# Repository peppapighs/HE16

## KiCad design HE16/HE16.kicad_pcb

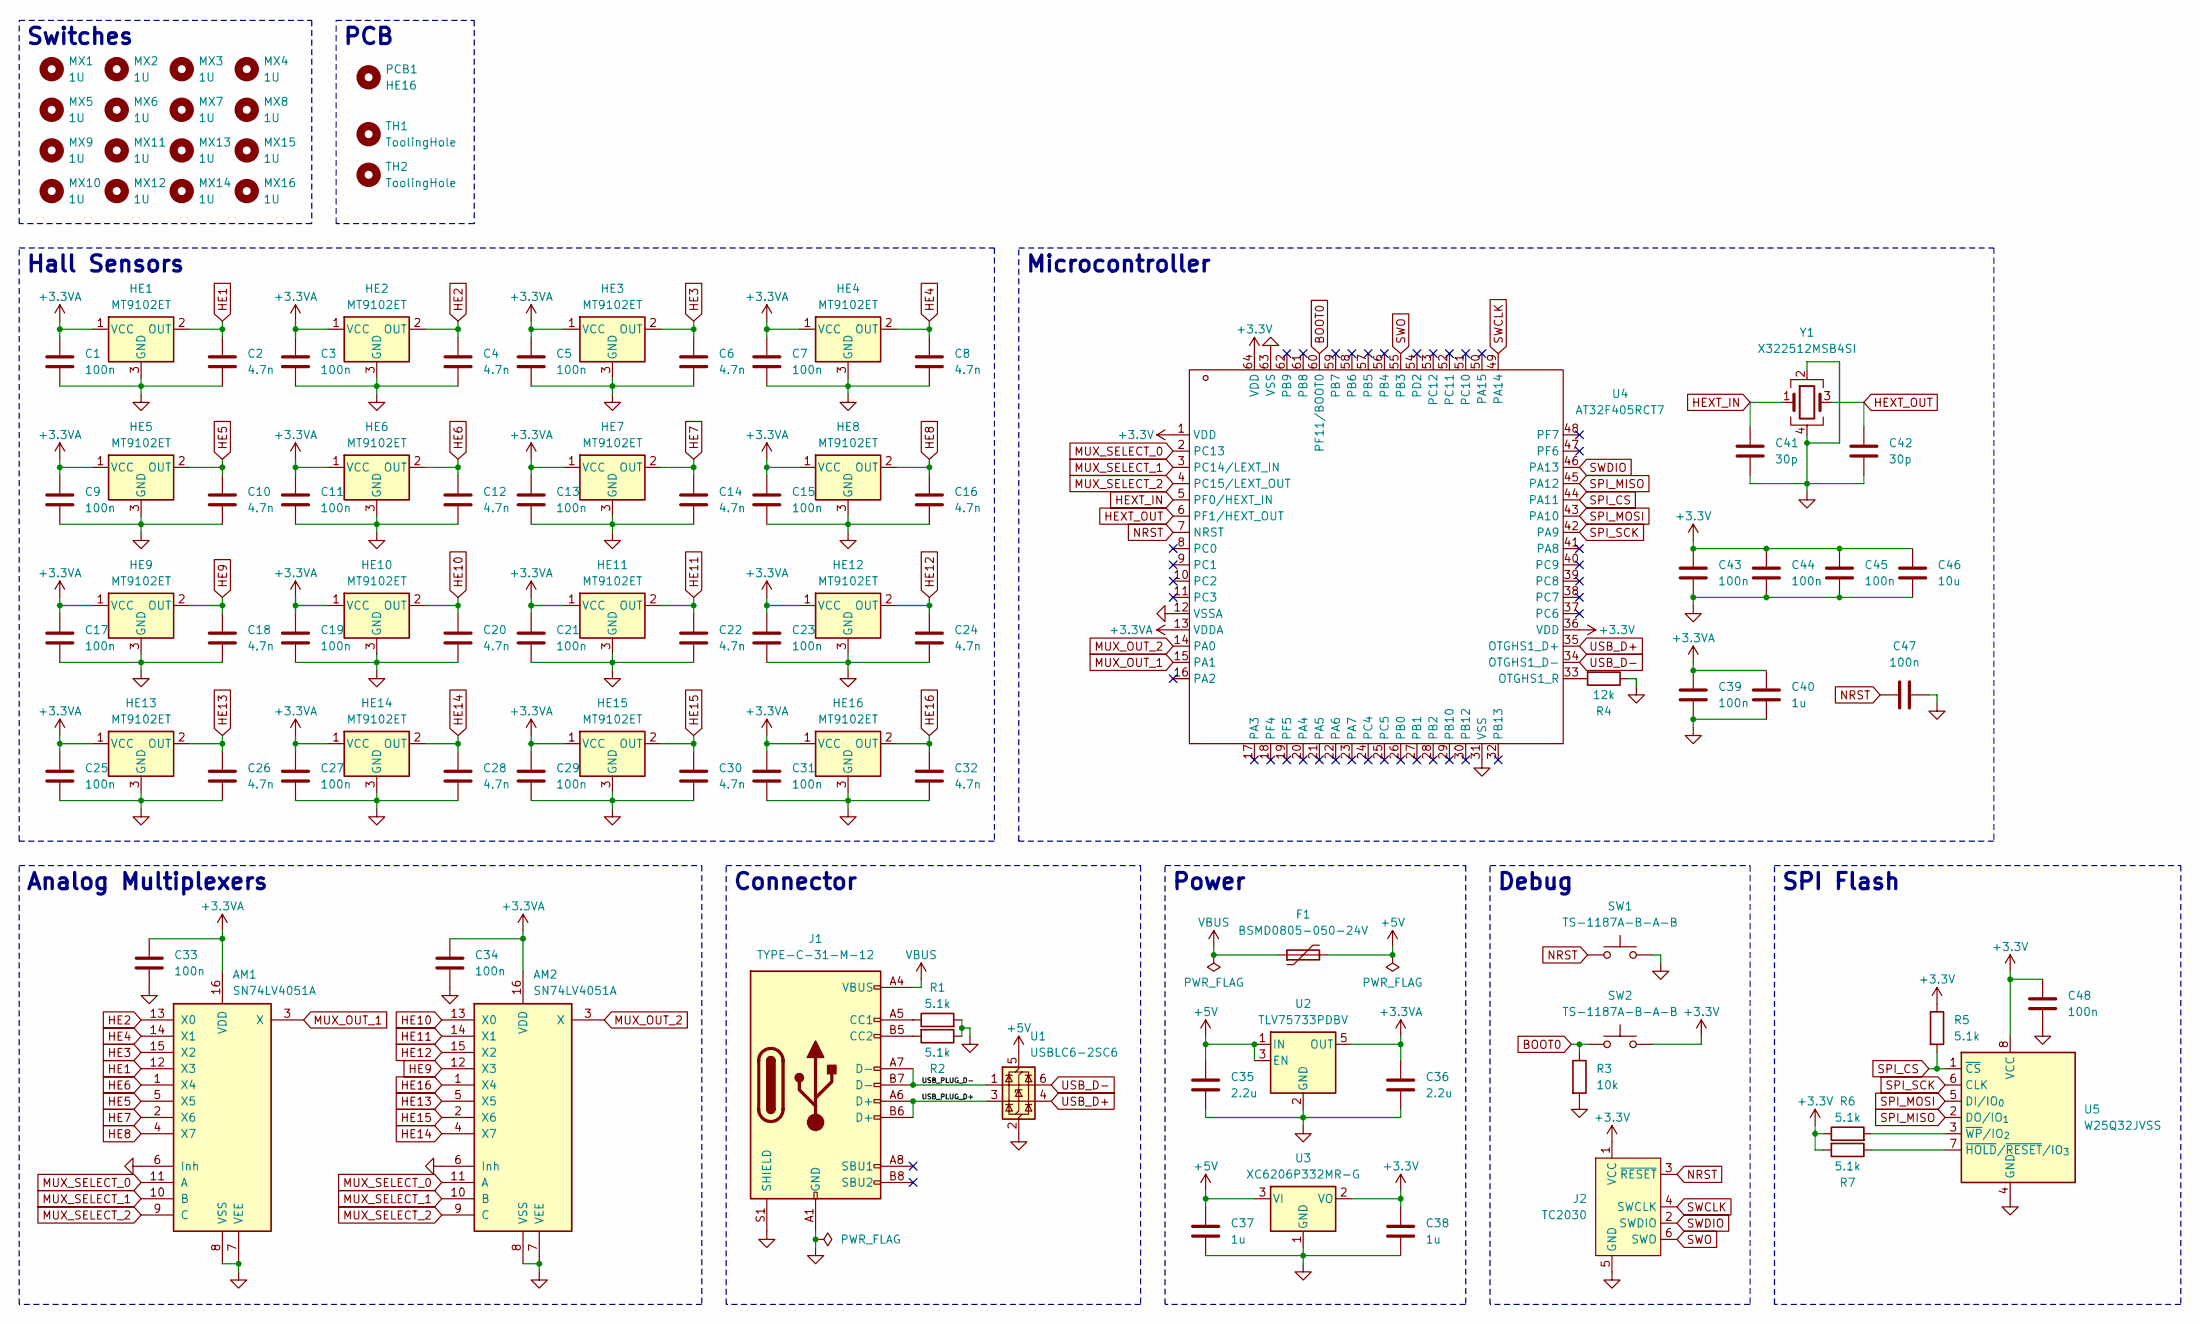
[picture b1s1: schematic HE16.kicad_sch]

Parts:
AM1, AM2: SN74LV4051A; TSSOP-16_4.4x5mm_P0.65mm
C1, C3, C5, C7, C9, C11, C13, C15, C17, C19, C21, C23, C25, C27, C29, C31, C33, C34, C39, C43, C44, C45, C47, C48: 100n; C_0402_1005Metric
C2, C4, C6, C8, C10, C12, C14, C16, C18, C20, C22, C24, C26, C28, C30, C32: 4.7n; C_0402_1005Metric
C35, C36: 2.2u; C_0603_1608Metric
C37, C38, C40: 1u; C_0603_1608Metric
C41, C42: 30p; C_0603_1608Metric
C46: 10u; C_0603_1608Metric
F1: BSMD0805-050-24V; Fuse_0805_2012Metric
HE1, HE2, HE3, HE4, HE5, HE6, HE7, HE8, HE9, HE10, HE11, HE12, HE13, HE14, HE15, HE16: MT9102ET; SOT-23-3
J1: TYPE-C-31-M-12; USB_C_Receptacle_HRO_TYPE-C-31-M-12
J2: TC2030; Tag-Connect_TC2030-IDC-FP_2x03_P1.27mm_Vertical
MX1, MX2, MX3, MX4, MX5, MX6, MX7, MX8, MX9, MX10, MX11, MX12, MX13, MX14, MX15, MX16: 1U; MX-1U
PCB1: HE16
R1, R2, R5, R6, R7: 5.1k; R_0402_1005Metric
R3: 10k; R_0402_1005Metric
R4: 12k; R_0402_1005Metric
SW1, SW2: TS-1187A-B-A-B; SW_Push_1P1T_XKB_TS-1187A
TH1, TH2: ToolingHole
U1: USBLC6-2SC6; SOT-23-6
U2: TLV75733PDBV; SOT-23-5
U3: XC6206P332MR-G; SOT-23-3
U4: AT32F405RCT7; LQFP-64_10x10mm_P0.5mm
U5: W25Q32JVSS; SOIC-8_5.3x5.3mm_P1.27mm
Y1: X322512MSB4SI; Crystal_SMD_3225-4Pin_3.2x2.5mm

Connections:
+3.3V: C38.1, C43.1, C44.1, C45.1, C46.1, C48.1, J2.1 (VCC), R5.1, R6.1, R7.2, SW2.2, U3.2 (VO), U4.1 (VDD), U4.36 (VDD), U4.64 (VDD), U5.8 (VCC)
+3.3VA: AM1.16 (VDD), AM2.16 (VDD), C1.1, C3.1, C5.1, C7.1, C9.1, C11.1, C13.1, C15.1, C17.1, C19.1, C21.1, C23.1, C25.1, C27.1, C29.1, C31.1, C33.1, C34.1, C36.1, C39.1, C40.1, HE1.1 (VCC), HE2.1 (VCC), HE3.1 (VCC), HE4.1 (VCC), HE5.1 (VCC), HE6.1 (VCC), HE7.1 (VCC), HE8.1 (VCC), HE9.1 (VCC), HE10.1 (VCC), HE11.1 (VCC), HE12.1 (VCC), HE13.1 (VCC), HE14.1 (VCC), HE15.1 (VCC), HE16.1 (VCC), U2.5 (OUT), U4.13 (VDDA)
+5V: C35.1, C37.1, F1.2, U1.5 (VBUS), U2.1 (IN), U2.3 (EN), U3.3 (VI)
/USB_PLUG_D+: J1.A6 (D+), J1.B6 (D+), U1.3 (I/O2)
/USB_PLUG_D-: J1.A7 (D-), J1.B7 (D-), U1.1 (I/O1)
BOOT0: R3.1, SW2.1, U4.60 (PF11/BOOT0)
GND: AM1.6 (Inh), AM1.7 (VEE), AM1.8 (VSS), AM2.6 (Inh), AM2.7 (VEE), AM2.8 (VSS), C1.2, C2.2, C3.2, C4.2, C5.2, C6.2, C7.2, C8.2, C9.2, C10.2, C11.2, C12.2, C13.2, C14.2, C15.2, C16.2, C17.2, C18.2, C19.2, C20.2, C21.2, C22.2, C23.2, C24.2, C25.2, C26.2, C27.2, C28.2, C29.2, C30.2, C31.2, C32.2, C33.2, C34.2, C35.2, C36.2, C37.2, C38.2, C39.2, C40.2, C41.2, C42.2, C43.2, C44.2, C45.2, C46.2, C47.2, C48.2, HE1.3 (GND), HE2.3 (GND), HE3.3 (GND), HE4.3 (GND), HE5.3 (GND), HE6.3 (GND), HE7.3 (GND), HE8.3 (GND), HE9.3 (GND), HE10.3 (GND), HE11.3 (GND), HE12.3 (GND), HE13.3 (GND), HE14.3 (GND), HE15.3 (GND), HE16.3 (GND), J1.A1 (GND), J1.A12 (GND), J1.B1 (GND), J1.B12 (GND), J1.S1 (SHIELD), J2.5 (GND), R1.2, R2.1, R3.2, R4.1, SW1.2, U1.2 (GND), U2.2 (GND), U3.1 (GND), U4.12 (VSSA), U4.31 (VSS), U4.63 (VSS), U5.4 (GND), Y1.2, Y1.4
HE1: AM1.12 (X3), C2.1, HE1.2 (OUT)
HE2: AM1.13 (X0), C4.1, HE2.2 (OUT)
HE3: AM1.15 (X2), C6.1, HE3.2 (OUT)
HE4: AM1.14 (X1), C8.1, HE4.2 (OUT)
HE5: AM1.5 (X5), C10.1, HE5.2 (OUT)
HE6: AM1.1 (X4), C12.1, HE6.2 (OUT)
HE7: AM1.2 (X6), C14.1, HE7.2 (OUT)
HE8: AM1.4 (X7), C16.1, HE8.2 (OUT)
HE9: AM2.12 (X3), C18.1, HE9.2 (OUT)
HE10: AM2.13 (X0), C20.1, HE10.2 (OUT)
HE11: AM2.14 (X1), C22.1, HE11.2 (OUT)
HE12: AM2.15 (X2), C24.1, HE12.2 (OUT)
HE13: AM2.5 (X5), C26.1, HE13.2 (OUT)
HE14: AM2.4 (X7), C28.1, HE14.2 (OUT)
HE15: AM2.2 (X6), C30.1, HE15.2 (OUT)
HE16: AM2.1 (X4), C32.1, HE16.2 (OUT)
HEXT_IN: C41.1, U4.5 (PF0/HEXT_IN), Y1.1
HEXT_OUT: C42.1, U4.6 (PF1/HEXT_OUT), Y1.3
MUX_OUT_1: AM1.3 (X), U4.15 (PA1)
MUX_OUT_2: AM2.3 (X), U4.14 (PA0)
MUX_SELECT_0: AM1.11 (A), AM2.11 (A), U4.2 (PC13)
MUX_SELECT_1: AM1.10 (B), AM2.10 (B), U4.3 (PC14/LEXT_IN)
MUX_SELECT_2: AM1.9 (C), AM2.9 (C), U4.4 (PC15/LEXT_OUT)
NRST: C47.1, J2.3 (~RESET), SW1.1, U4.7 (NRST)
unnamed: J1.A5 (CC1), R1.1
unnamed: J1.B5 (CC2), R2.2
unnamed: R4.2, U4.33 (OTGHS1_R)
unnamed: R7.1, U5.7 (~HOLD/~RESET/IO_{3})
unnamed: R6.2, U5.3 (~WP/IO_{2})
SPI_CS: R5.2, U4.44 (PA11), U5.1 (~CS)
SPI_MISO: U4.45 (PA12), U5.2 (DO/IO_{1})
SPI_MOSI: U4.43 (PA10), U5.5 (DI/IO_{0})
SPI_SCK: U4.42 (PA9), U5.6 (CLK)
SWCLK: J2.4 (SWCLK), U4.49 (PA14)
SWDIO: J2.2 (SWDIO), U4.46 (PA13)
SWO: J2.6 (SWO), U4.55 (PB3)
USB_D+: U1.4 (I/O2), U4.35 (OTGHS1_D+)
USB_D-: U1.6 (I/O1), U4.34 (OTGHS1_D-)
VBUS: F1.1, J1.A4 (VBUS), J1.A9 (VBUS), J1.B4 (VBUS), J1.B9 (VBUS)

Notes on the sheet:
Switches
Connector
Debug
Microcontroller
Analog Multiplexers
Hall Sensors
PCB
SPI Flash
Power

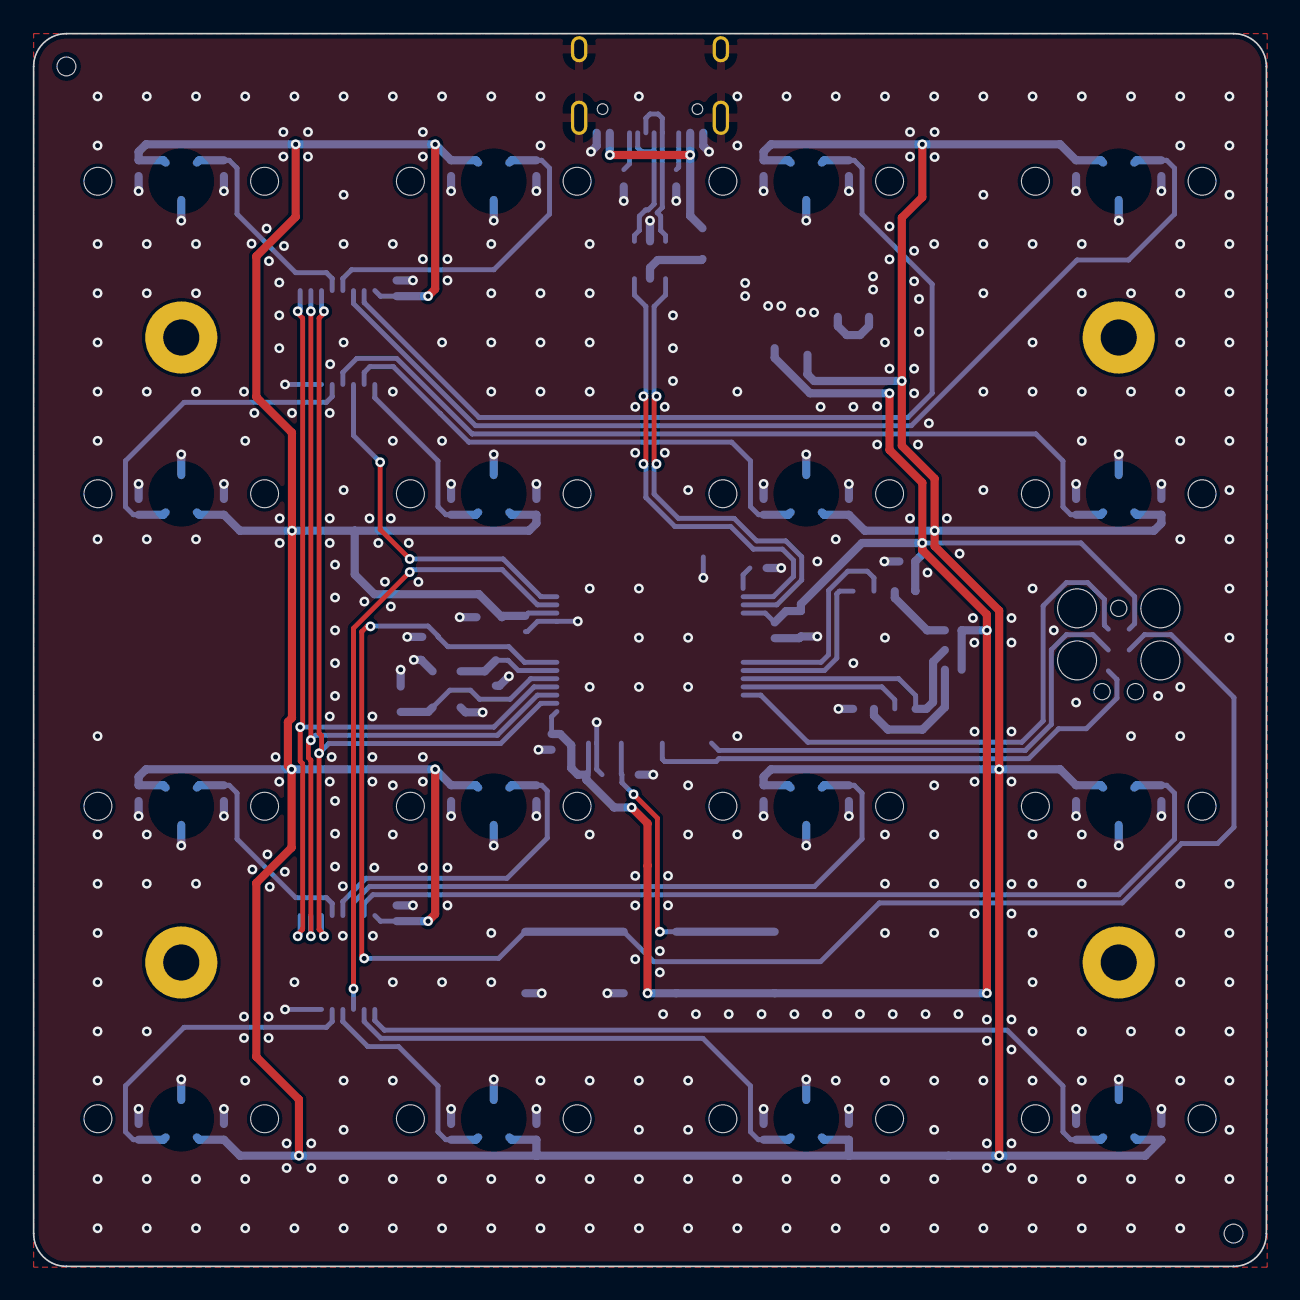
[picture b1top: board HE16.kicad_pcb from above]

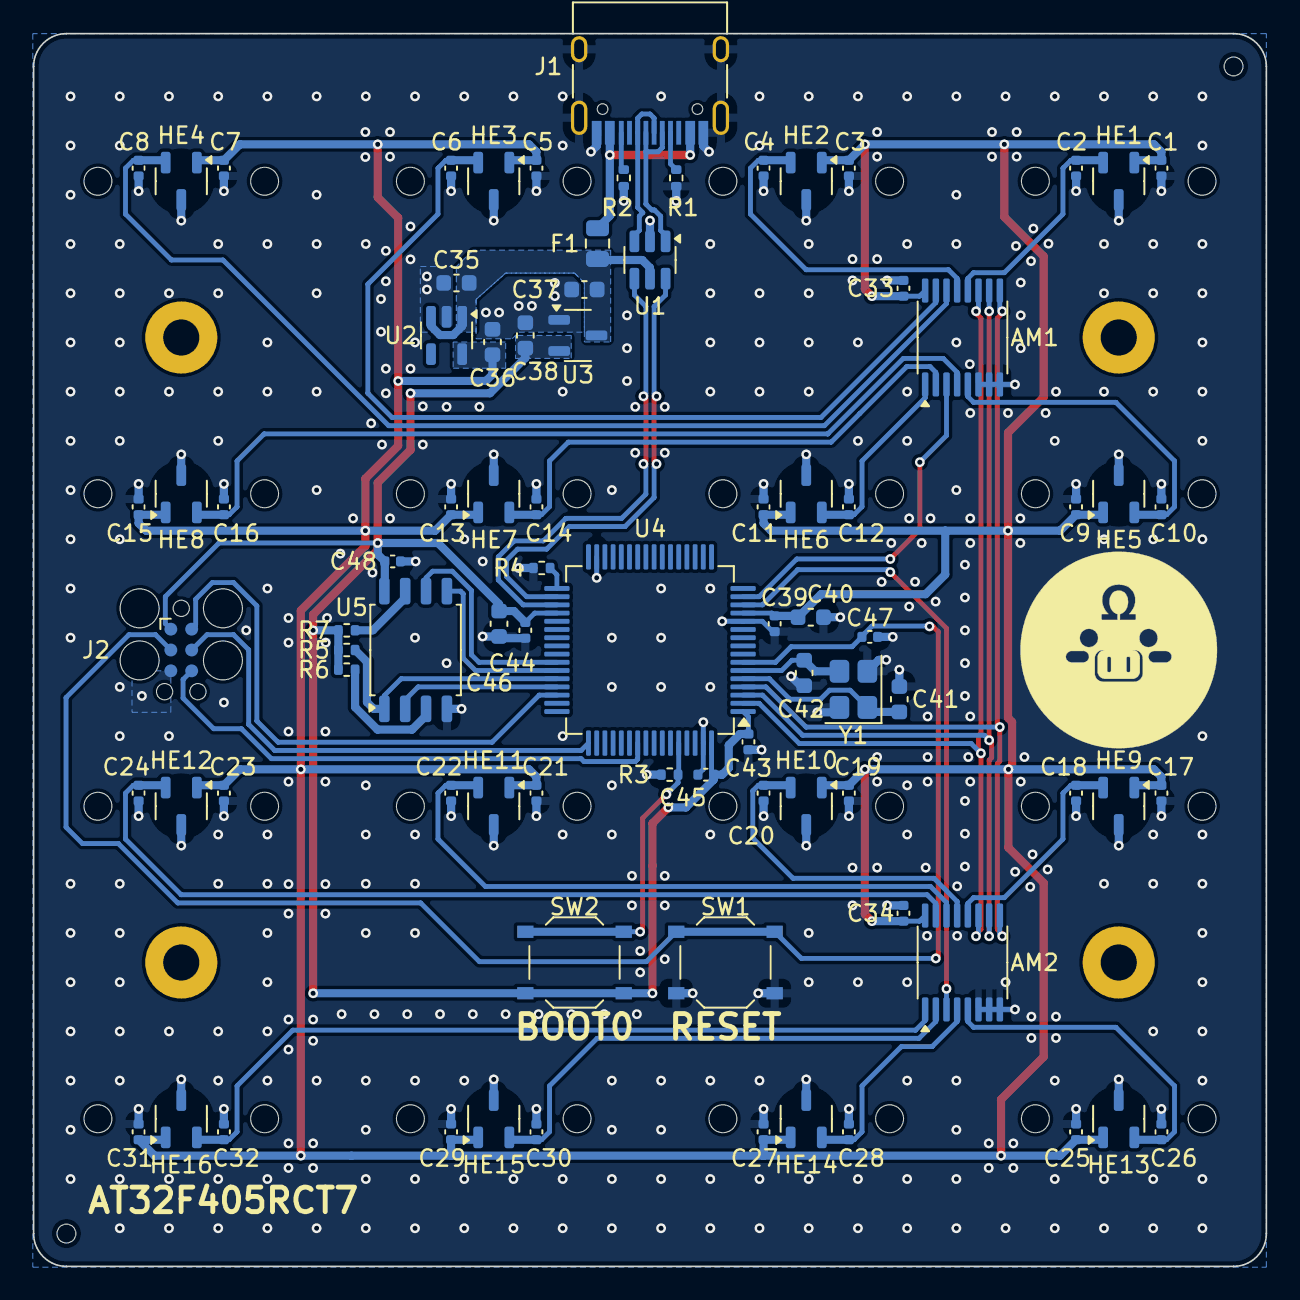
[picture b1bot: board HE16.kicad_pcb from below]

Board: 2 copper layers, 75.2 x 75.2 mm, 103 parts (86 on the bottom side), 46 nets.

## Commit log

2025-07-30 :tada: initialize project
2025-07-30 :memo: add LICENSE
